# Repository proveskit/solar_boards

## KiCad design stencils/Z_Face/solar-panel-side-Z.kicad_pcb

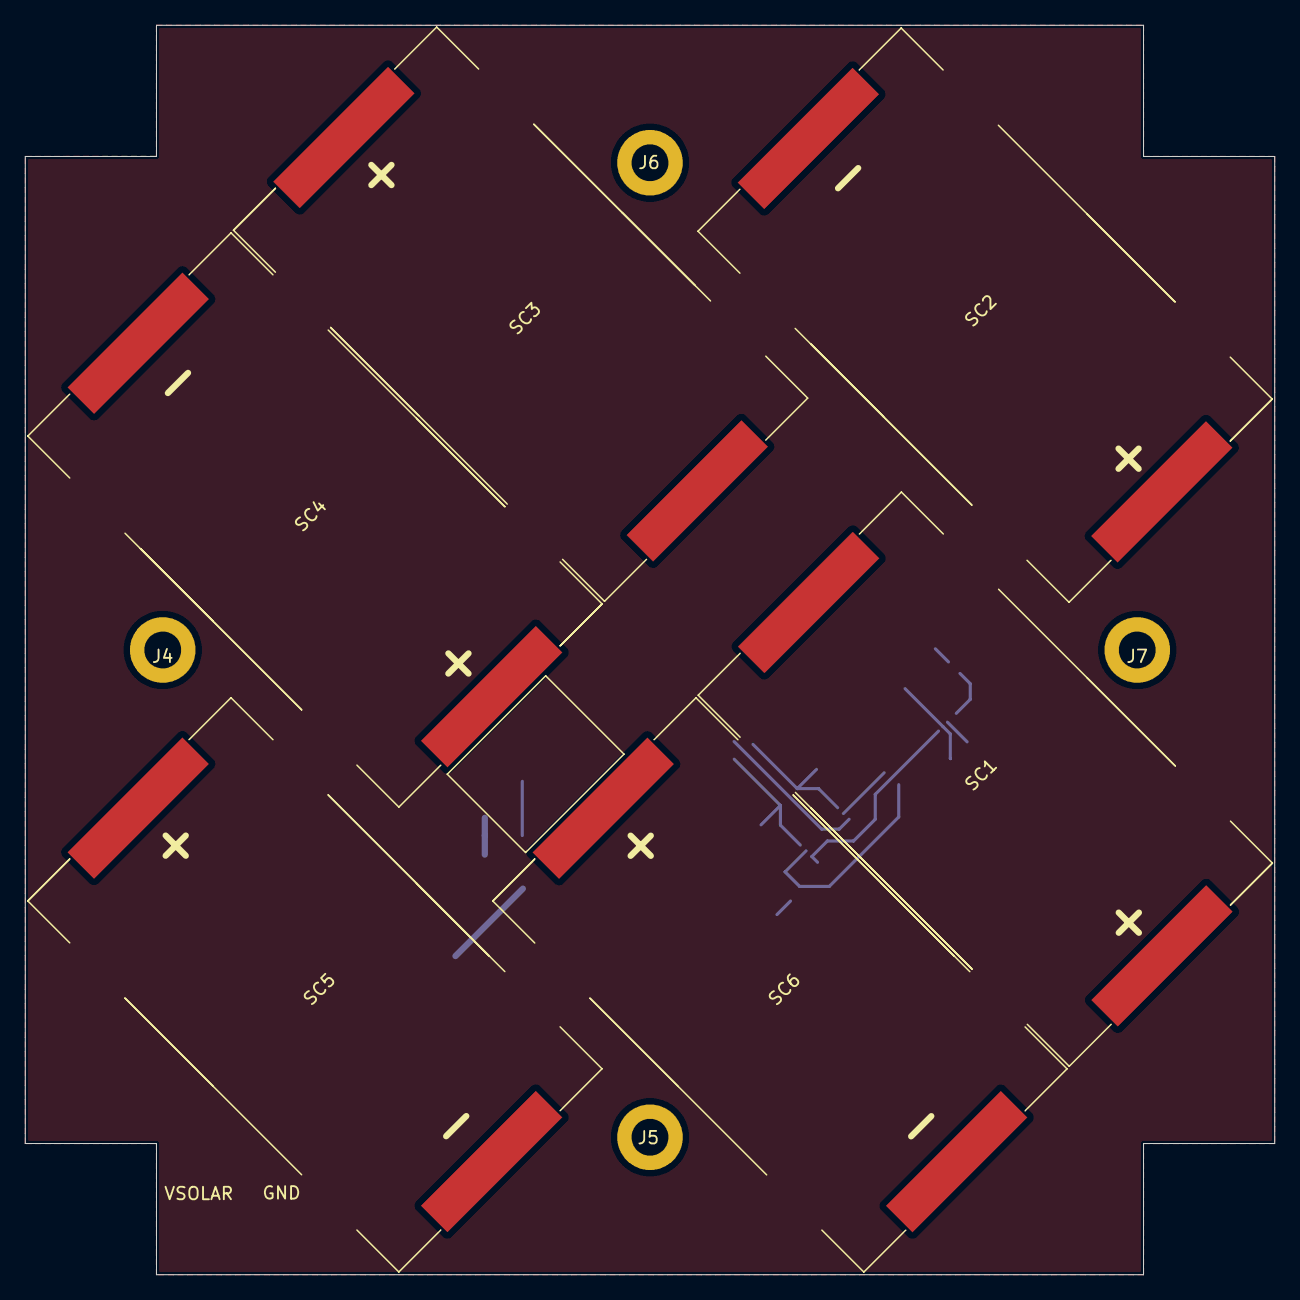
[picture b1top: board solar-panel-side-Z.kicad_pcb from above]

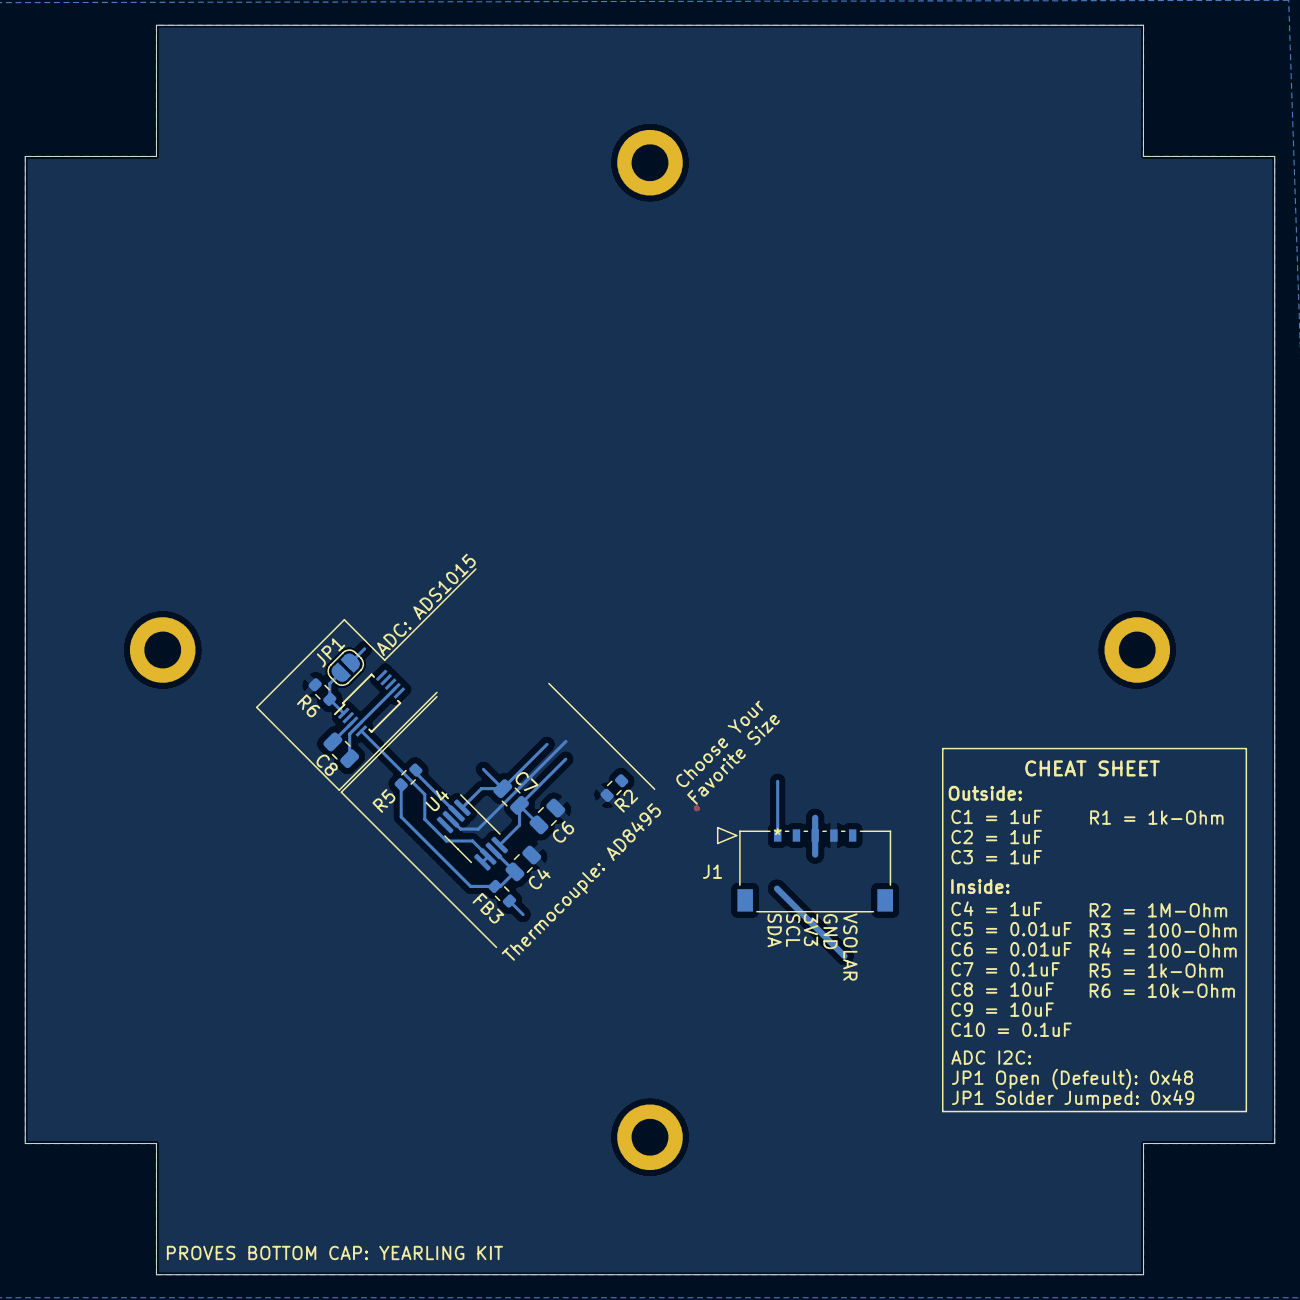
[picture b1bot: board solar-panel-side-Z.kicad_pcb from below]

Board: 4 copper layers, 100.0 x 100.0 mm, 22 parts (12 on the bottom side), 15 nets.

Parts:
C4: 1uF; C_0805_2012Metric
C6: 0.01uF; C_0805_2012Metric
C7: 0.1uF; C_0805_2012Metric
C8: 10uF; C_0805_2012Metric
FB3: FerriteBead; R_0603_1608Metric
J1: CON-5040500591; CON_5040500591
J4, J5, J6, J7: Conn_01x01; MountingHoles
JP1: SolderJumper_2_Open; SolderJumper-2_P1.3mm_Open_RoundedPad1.0x1.5mm
R2: 1-MOhm; R_0603_1608Metric
R5: 1k; R_0603_1608Metric
R6: 10k-Ohm; R_0603_1608Metric
SC1, SC2, SC3, SC4, SC5, SC6: SM101K07TF; KXOB101K08F-TR
U4: AD8495; MSOP-8_3x3mm_P0.65mm
U5: ADS1015IDGS; TSSOP-10_3x3mm_P0.5mm

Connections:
+3V3: FB3.2, J1.3, JP1.2 (B)
AGND: C8.2, U5.3 (GND)
AVDD: C8.1, U5.4 (AIN0), U5.6 (AIN2), U5.7 (AIN3), U5.8 (VDD)
GND: C4.2, C6.2, J1.4, R2.2, R6.1, SC2.2 (-), SC4.2 (-), SC6.2 (-), U4.3 (-Vs)
unnamed: C4.1, FB3.1, R5.2, U4.7 (+Vs)
unnamed: C7.2, U4.1 (-IN)
unnamed: C6.1, C7.1, U4.8 (+IN)
unnamed: JP1.1 (A), R6.2, U5.1 (ADDR)
unnamed: R5.1, U4.2 (REF)
unnamed: SC1.2 (-), SC2.1 (+)
unnamed: SC3.2 (-), SC4.1 (+)
unnamed: SC5.2 (-), SC6.1 (+)
OUT: U4.5 (SENSE), U4.6, U5.5 (AIN1)
SCL: J1.2, U5.10 (SCL)
SDA: J1.1, U5.9 (SDA)

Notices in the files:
parts and their libraries:
Copyright 2021 Accelerated Designs. All rights reserved.
